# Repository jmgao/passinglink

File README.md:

Moved to [passinglink/passinglink](https://github.com/passinglink/passinglink)

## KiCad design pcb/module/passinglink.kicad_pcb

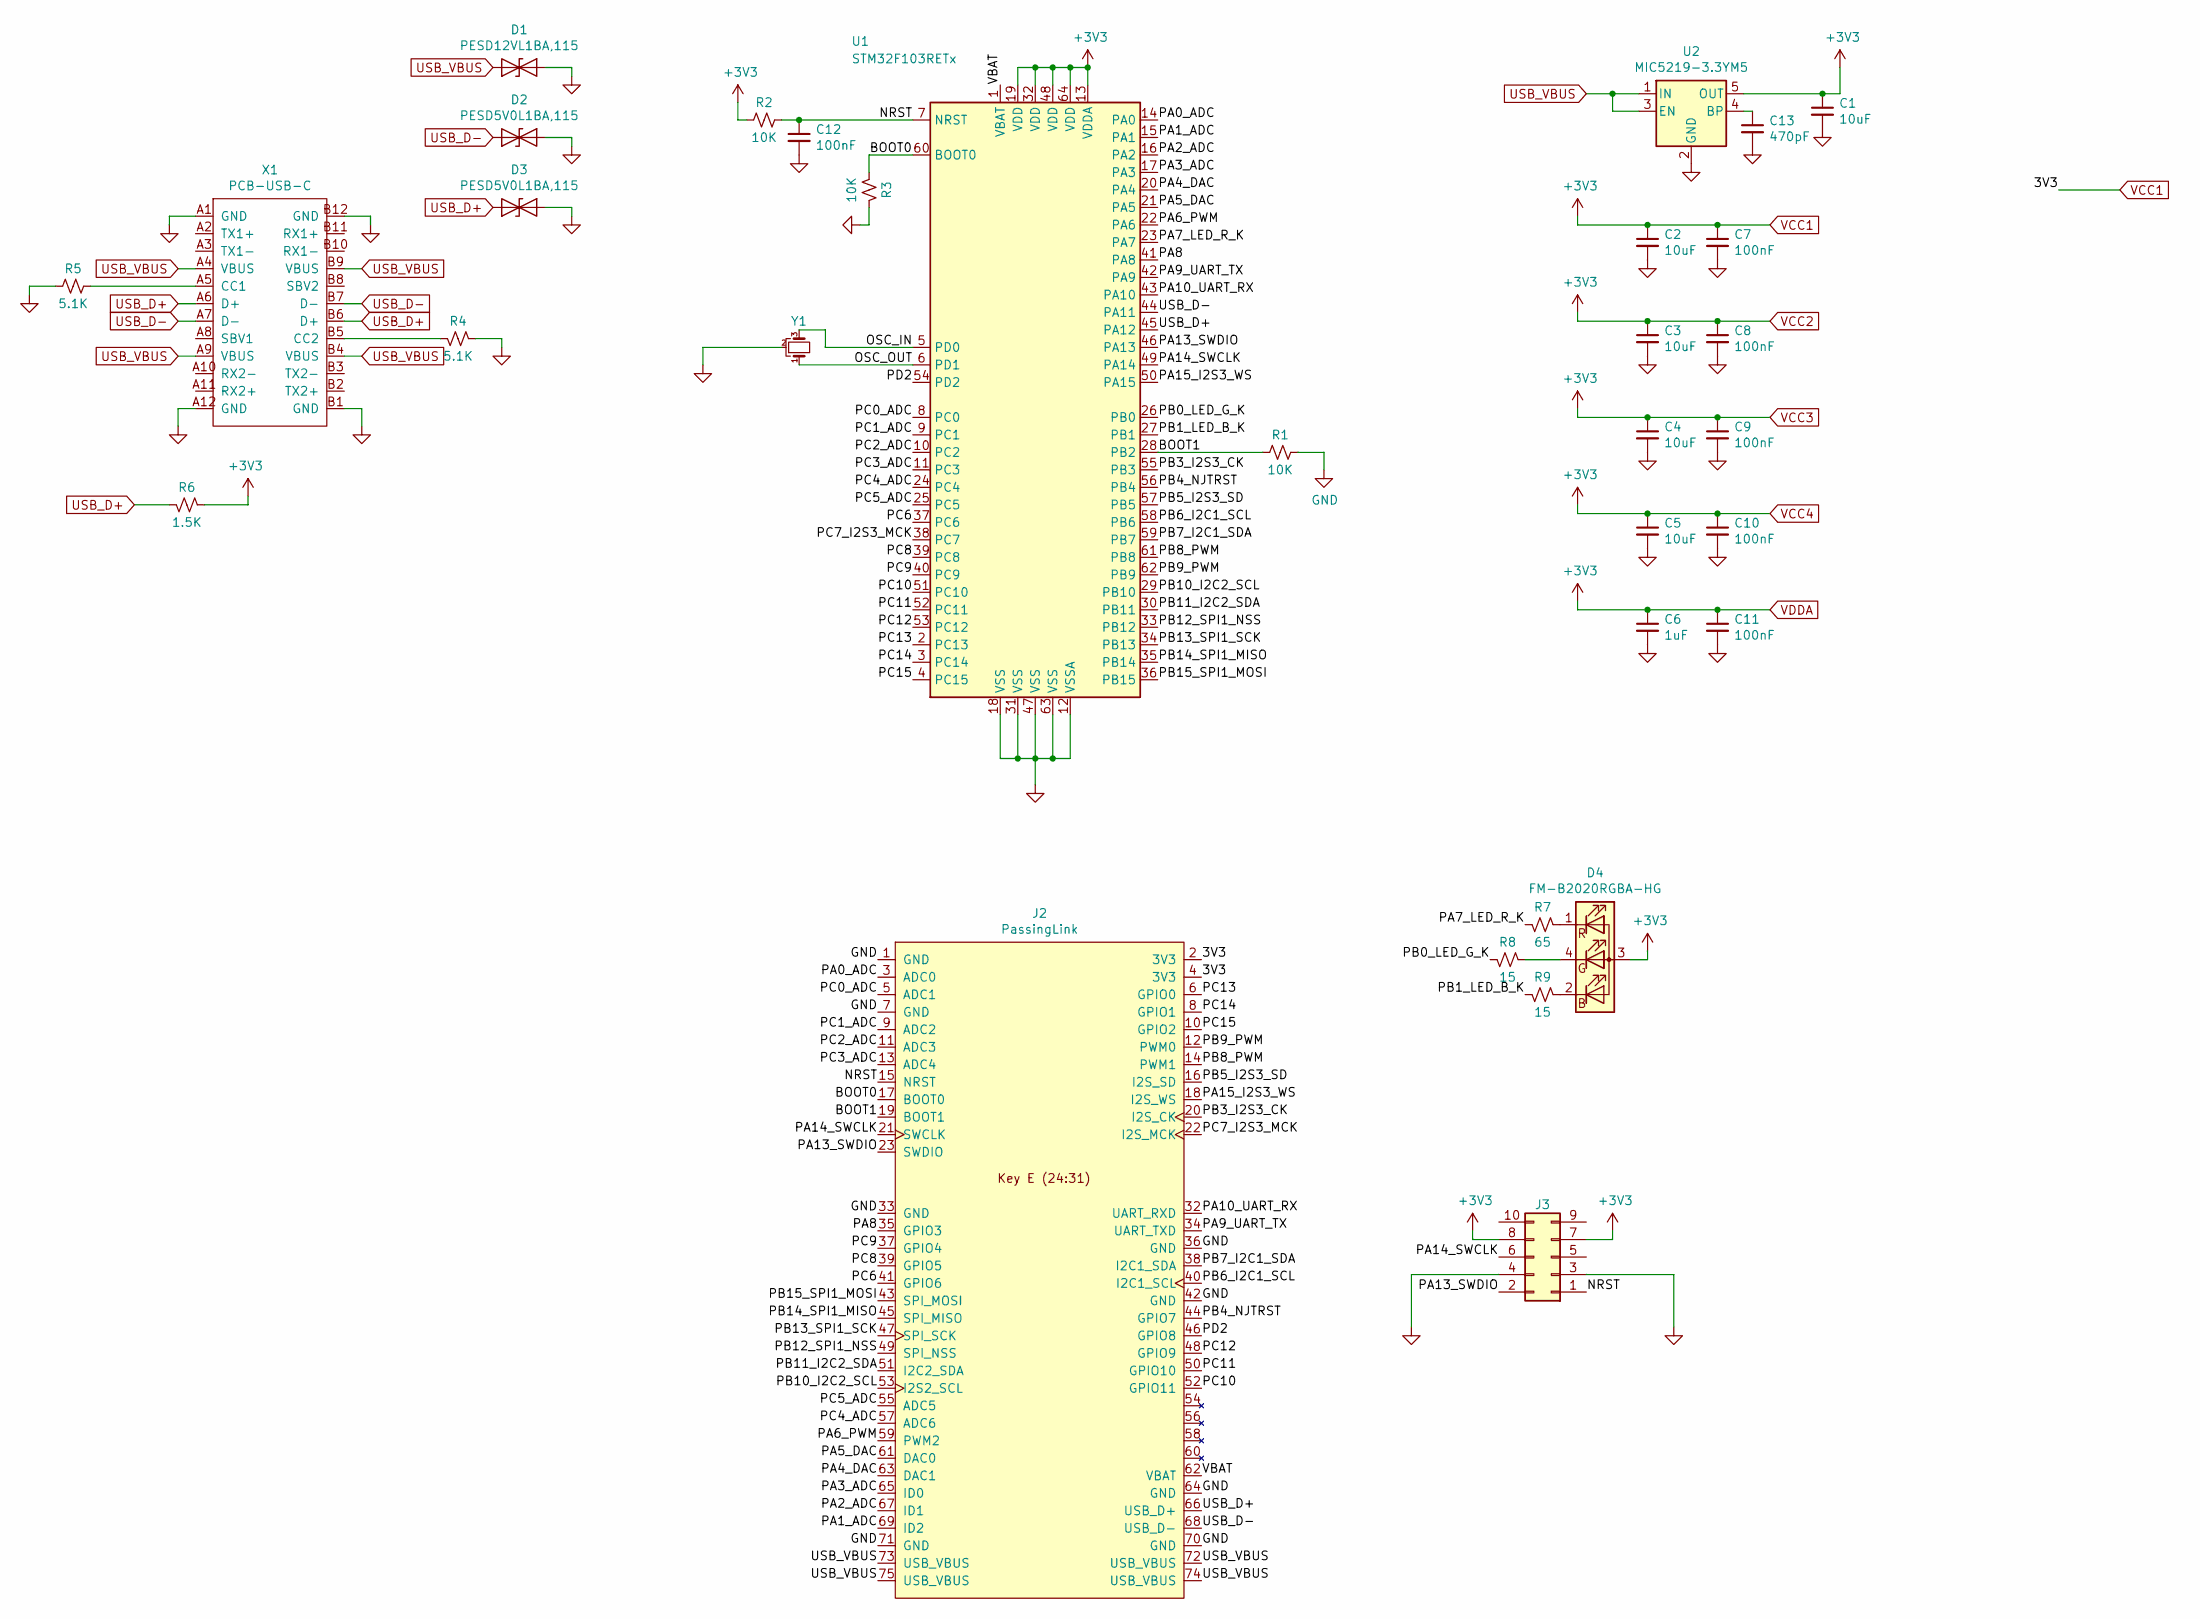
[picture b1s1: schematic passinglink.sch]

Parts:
C1, C2, C3, C4, C5: 10uF; C_0603_1608Metric
C6: 1uF; C_0603_1608Metric
C7, C8, C9, C10, C11, C12: 100nF; C_0603_1608Metric
C13: 470pF; C_0603_1608Metric
D1: PESD12VL1BA,115; D_SOD-323
D2, D3: PESD5V0L1BA,115; D_SOD-323
D4: FM-B2020RGBA-HG
J2: PassingLink; NGFF_E
J3: Conn_02x05_Odd_Even; Tag-Connect_TC2050-IDC-NL_2x05_P1.27mm_Vertical
R1, R2, R3: 10K; R_0603_1608Metric
R4, R5: 5.1K; R_0603_1608Metric
R6: 1.5K; R_0603_1608Metric
R7: 65; R_0603_1608Metric
R8, R9: 15; R_0603_1608Metric
U1: STM32F103RETx; LQFP-64_10x10mm_P0.5mm
U2: MIC5219-3.3YM5; SOT-23-5
X1: PCB-USB-C
Y1: Crystal_GND2_Small; Resonator_SMD_muRata_CSTxExxV-3Pin_3.0x1.1mm

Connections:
/BOOT0: J2.17 (BOOT0), R3.1, U1.60 (BOOT0)
/BOOT1: J2.19 (BOOT1), R1.2, U1.28 (PB2)
/NRST: C12.1, J2.15 (NRST), J3.1, R2.1, U1.7 (NRST)
/OSC_IN: U1.5 (PD0), Y1.3
/OSC_OUT: U1.6 (PD1), Y1.1
/PA0_ADC: J2.3 (ADC0), U1.14 (PA0)
/PA1_ADC: J2.69 (ID2), U1.15 (PA1)
/PA2_ADC: J2.67 (ID1), U1.16 (PA2)
/PA3_ADC: J2.65 (ID0), U1.17 (PA3)
/PA4_DAC: J2.63 (DAC1), U1.20 (PA4)
/PA5_DAC: J2.61 (DAC0), U1.21 (PA5)
/PA6_PWM: J2.59 (PWM2), U1.22 (PA6)
/PA7_LED_R_K: R7.1, U1.23 (PA7)
/PA8: J2.35 (GPIO3), U1.41 (PA8)
/PA9_UART_TX: J2.34 (UART_TXD), U1.42 (PA9)
/PA10_UART_RX: J2.32 (UART_RXD), U1.43 (PA10)
/PA13_SWDIO: J2.23 (SWDIO), J3.2, U1.46 (PA13)
/PA14_SWCLK: J2.21 (SWCLK), J3.6, U1.49 (PA14)
/PA15_I2S3_WS: J2.18 (I2S_WS), U1.50 (PA15)
/PB0_LED_G_K: R8.1, U1.26 (PB0)
/PB1_LED_B_K: R9.1, U1.27 (PB1)
/PB3_I2S3_CK: J2.20 (I2S_CK), U1.55 (PB3)
/PB4_NJTRST: J2.44 (GPIO7), U1.56 (PB4)
/PB5_I2S3_SD: J2.16 (I2S_SD), U1.57 (PB5)
/PB6_I2C1_SCL: J2.40 (I2C1_SCL), U1.58 (PB6)
/PB7_I2C1_SDA: J2.38 (I2C1_SDA), U1.59 (PB7)
/PB8_PWM: J2.14 (PWM1), U1.61 (PB8)
/PB9_PWM: J2.12 (PWM0), U1.62 (PB9)
/PB10_I2C2_SCL: J2.53 (I2S2_SCL), U1.29 (PB10)
/PB11_I2C2_SDA: J2.51 (I2C2_SDA), U1.30 (PB11)
/PB12_SPI1_NSS: J2.49 (SPI_NSS), U1.33 (PB12)
/PB13_SPI1_SCK: J2.47 (SPI_SCK), U1.34 (PB13)
/PB14_SPI1_MISO: J2.45 (SPI_MISO), U1.35 (PB14)
/PB15_SPI1_MOSI: J2.43 (SPI_MOSI), U1.36 (PB15)
/PC0_ADC: J2.5 (ADC1), U1.8 (PC0)
/PC1_ADC: J2.9 (ADC2), U1.9 (PC1)
/PC2_ADC: J2.11 (ADC3), U1.10 (PC2)
/PC3_ADC: J2.13 (ADC4), U1.11 (PC3)
/PC4_ADC: J2.57 (ADC6), U1.24 (PC4)
/PC5_ADC: J2.55 (ADC5), U1.25 (PC5)
/PC6: J2.41 (GPIO6), U1.37 (PC6)
/PC7_I2S3_MCK: J2.22 (I2S_MCK), U1.38 (PC7)
/PC8: J2.39 (GPIO5), U1.39 (PC8)
/PC9: J2.37 (GPIO4), U1.40 (PC9)
/PC10: J2.52 (GPIO11), U1.51 (PC10)
/PC11: J2.50 (GPIO10), U1.52 (PC11)
/PC12: J2.48 (GPIO9), U1.53 (PC12)
/PC13: J2.6 (GPIO0), U1.2 (PC13)
/PC14: J2.8 (GPIO1), U1.3 (PC14)
/PC15: J2.10 (GPIO2), U1.4 (PC15)
/PD2: J2.46 (GPIO8), U1.54 (PD2)
/VBAT: J2.62 (VBAT), U1.1 (VBAT)
GND: C1.2, C2.2, C3.2, C4.2, C5.2, C6.2, C7.2, C8.2, C9.2, C10.2, C11.2, C12.2, C13.2, D1.2 (A2), D2.2 (A2), D3.2 (A2), J2.1 (GND), J2.7 (GND), J2.33 (GND), J2.36 (GND), J2.42 (GND), J2.64 (GND), J2.70 (GND), J2.71 (GND), J3.3, J3.4, R1.1, R3.2, R4.2, R5.2, U1.12 (VSSA), U1.18 (VSS), U1.31 (VSS), U1.47 (VSS), U1.63 (VSS), U2.2 (GND), X1.A1 (GND), X1.A12 (GND), X1.B1 (GND), X1.B12 (GND), Y1.2
unnamed: C13.1, U2.4 (BP)
unnamed: D4.1 (R-), R7.2
unnamed: D4.2 (B-), R9.2
unnamed: D4.4 (G-), R8.2
unnamed: R4.1, X1.B5 (CC2)
unnamed: R5.1, X1.A5 (CC1)
USB_D+: D3.1 (A1), J2.66 (USB_D+), R6.1, U1.45 (PA12), X1.A6 (D+), X1.B6 (D+)
USB_D-: D2.1 (A1), J2.68 (USB_D-), U1.44 (PA11), X1.A7 (D-), X1.B7 (D-)
USB_VBUS: D1.1 (A1), J2.72 (USB_VBUS), J2.73 (USB_VBUS), J2.74 (USB_VBUS), J2.75 (USB_VBUS), U2.1 (IN), U2.3 (EN), X1.A4 (VBUS), X1.A9 (VBUS), X1.B4 (VBUS), X1.B9 (VBUS)
VCC1: C1.1, C2.1, C3.1, C4.1, C5.1, C6.1, C7.1, C8.1, C9.1, C10.1, C11.1, D4.3 (+), J2.2 (3V3), J2.4 (3V3), J3.7, J3.8, R2.2, R6.2, U1.13 (VDDA), U1.19 (VDD), U1.32 (VDD), U1.48 (VDD), U1.64 (VDD), U2.5 (OUT)

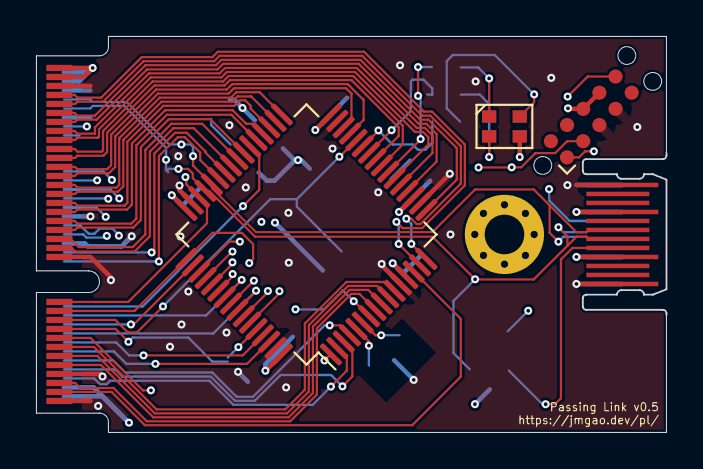
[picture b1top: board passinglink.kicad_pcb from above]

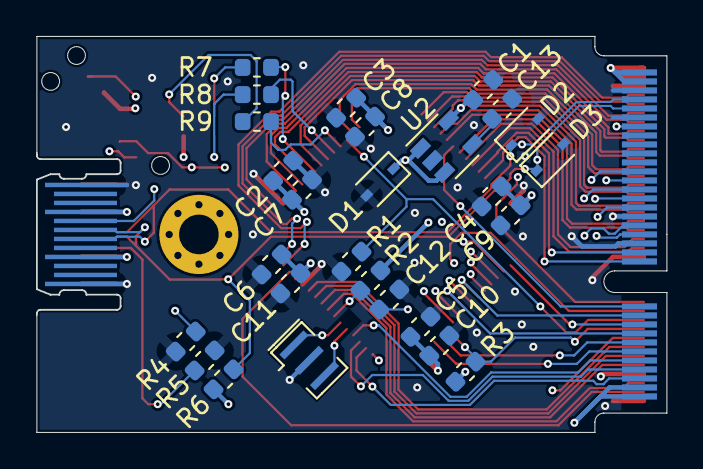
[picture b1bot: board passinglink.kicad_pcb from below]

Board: 4 copper layers, 35.0 x 22.0 mm, 33 parts (27 on the bottom side), 63 nets.

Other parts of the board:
H1: MountingHole_2.2mm_M2_Pad_Via

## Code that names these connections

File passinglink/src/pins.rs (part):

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  use stm32f1xx_hal::gpio::{Input, Output, PullUp, PushPull};

  pub struct InputPins {
    pub stick_down: PB5<Input<PullUp>>,
    pub stick_up: PB6<Input<PullUp>>,
    pub stick_left: PB7<Input<PullUp>>,
    pub stick_right: PB8<Input<PullUp>>,

    pub button_north: PC11<Input<PullUp>>,
    pub button_east: PA9<Input<PullUp>>,
    pub button_south: PA10<Input<PullUp>>,
    pub button_west: PC10<Input<PullUp>>,

    pub button_l1: PD2<Input<PullUp>>,
    pub button_r1: PC12<Input<PullUp>>,

    pub button_l2: PC9<Input<PullUp>>,
    pub button_r2: PA8<Input<PullUp>>,

    pub button_l3: PA7<Input<PullUp>>,
    pub button_r3: PB11<Input<PullUp>>,

    pub button_home: PB1<Input<PullUp>>,
    pub button_start: PC7<Input<PullUp>>,
    pub button_select: PC8<Input<PullUp>>,

    pub button_trackpad: PA6<Input<PullUp>>,

    pub mode_lock: PB0<Input<PullUp>>,
    pub mode_ls: PC5<Input<PullUp>>,
    pub mode_rs: PC4<Input<PullUp>>,
    pub mode_ps3: PB10<Input<PullUp>>,
  }

  macro_rules! assign_inputs {
    ($gpioa: expr, $gpiob: expr, $gpioc: expr, $gpiod: expr) => {{
      InputPins {
        stick_down: $gpiob.pb5.into_pull_up_input(&mut $gpiob.crl),
        stick_up: $gpiob.pb6.into_pull_up_input(&mut $gpiob.crl),
        stick_left: $gpiob.pb7.into_pull_up_input(&mut $gpiob.crl),
        stick_right: $gpiob.pb8.into_pull_up_input(&mut $gpiob.crh),

        button_north: $gpioc.pc11.into_pull_up_input(&mut $gpioc.crh),
        button_east: $gpioa.pa9.into_pull_up_input(&mut $gpioa.crh),
        button_south: $gpioa.pa10.into_pull_up_input(&mut $gpioa.crh),
        button_west: $gpioc.pc10.into_pull_up_input(&mut $gpioc.crh),

        button_l1: $gpiod.pd2.into_pull_up_input(&mut $gpiod.crl),
        button_r1: $gpioc.pc12.into_pull_up_input(&mut $gpioc.crh),

        button_l2: $gpioc.pc9.into_pull_up_input(&mut $gpioc.crh),
        button_r2: $gpioa.pa8.into_pull_up_input(&mut $gpioa.crh),

        button_l3: $gpioa.pa7.into_pull_up_input(&mut $gpioa.crl),
        button_r3: $gpiob.pb11.into_pull_up_input(&mut $gpiob.crh),

        button_home: $gpiob.pb1.into_pull_up_input(&mut $gpiob.crl),
        button_start: $gpioc.pc7.into_pull_up_input(&mut $gpioc.crl),
        button_select: $gpioc.pc8.into_pull_up_input(&mut $gpioc.crh),
        button_trackpad: $gpioa.pa6.into_pull_up_input(&mut $gpioa.crl),

        mode_lock: $gpiob.pb0.into_pull_up_input(&mut $gpiob.crl),
        mode_ls: $gpioc.pc5.into_pull_up_input(&mut $gpioc.crl),
        mode_rs: $gpioc.pc4.into_pull_up_input(&mut $gpioc.crl),
        mode_ps3: $gpiob.pb10.into_pull_up_input(&mut $gpiob.crh),
      }
    }};
  }

  pub struct LedPins {
    pub front: PC6<Output<PushPull>>,
    pub pcb_r: Option<PCx<Output<PushPull>>>,
    pub pcb_g: Option<PCx<Output<PushPull>>>,
    pub pcb_b: Option<PCx<Output<PushPull>>>,
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  macro_rules! assign_leds {
    ($gpioa: expr, $gpiob: expr, $gpioc: expr, $gpiod: expr) => {{
      LedPins {
        front: $gpioc.pc6.into_push_pull_output(&mut $gpioc.crl),
        pcb_r: None,
        pcb_g: None,
        pcb_b: None,
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  use stm32f1xx_hal::gpio::{Input, Output, PullUp, PushPull};

  pub struct InputPins {
    pub stick_down: PA10<Input<PullUp>>,
    pub stick_up: PA9<Input<PullUp>>,
    pub stick_left: PA8<Input<PullUp>>,
    pub stick_right: PC9<Input<PullUp>>,

    pub button_north: PC6<Input<PullUp>>,
    pub button_east: PB13<Input<PullUp>>,
    pub button_south: PB14<Input<PullUp>>,
    pub button_west: PB15<Input<PullUp>>,

    pub button_l1: PC8<Input<PullUp>>,
    pub button_r1: PC7<Input<PullUp>>,

    pub button_l2: PB11<Input<PullUp>>,
    pub button_r2: PB12<Input<PullUp>>,

    pub button_l3: PC12<Input<PullUp>>,
    pub button_r3: PD2<Input<PullUp>>,

    pub button_home: PC15<Input<PullUp>>,
    pub button_start: PC4<Input<PullUp>>,
    pub button_select: PB10<Input<PullUp>>,
    pub button_trackpad: PB5<Input<PullUp>>,

    pub mode_lock: PC14<Input<PullUp>>,
    pub mode_ls: PC13<Input<PullUp>>,
    pub mode_rs: PC10<Input<PullUp>>,
    pub mode_ps3: PC11<Input<PullUp>>,
  }

  macro_rules! assign_inputs {
    ($gpioa: expr, $gpiob: expr, $gpioc: expr, $gpiod: expr) => {{
      InputPins {
        stick_down: $gpioa.pa10.into_pull_up_input(&mut $gpioa.crh),
        stick_up: $gpioa.pa9.into_pull_up_input(&mut $gpioa.crh),
        stick_left: $gpioa.pa8.into_pull_up_input(&mut $gpioa.crh),
        stick_right: $gpioc.pc9.into_pull_up_input(&mut $gpioc.crh),

        button_north: $gpioc.pc6.into_pull_up_input(&mut $gpioc.crl),
        button_east: $gpiob.pb13.into_pull_up_input(&mut $gpiob.crh),
        button_south: $gpiob.pb14.into_pull_up_input(&mut $gpiob.crh),
        button_west: $gpiob.pb15.into_pull_up_input(&mut $gpiob.crh),

        button_l1: $gpioc.pc8.into_pull_up_input(&mut $gpioc.crh),
        button_r1: $gpioc.pc7.into_pull_up_input(&mut $gpioc.crl),

        button_l2: $gpiob.pb11.into_pull_up_input(&mut $gpiob.crh),
        button_r2: $gpiob.pb12.into_pull_up_input(&mut $gpiob.crh),

        button_l3: $gpioc.pc12.into_pull_up_input(&mut $gpioc.crh),
        button_r3: $gpiod.pd2.into_pull_up_input(&mut $gpiod.crl),

        button_home: $gpioc.pc15.into_pull_up_input(&mut $gpioc.crh),
        button_start: $gpioc.pc4.into_pull_up_input(&mut $gpioc.crl),
        button_select: $gpiob.pb10.into_pull_up_input(&mut $gpiob.crh),
        button_trackpad: $gpiob.pb5.into_pull_up_input(&mut $gpiob.crl),

        mode_lock: $gpioc.pc14.into_pull_up_input(&mut $gpioc.crh),
        mode_ls: $gpioc.pc13.into_pull_up_input(&mut $gpioc.crh),
        mode_rs: $gpioc.pc10.into_pull_up_input(&mut $gpioc.crh),
        mode_ps3: $gpioc.pc11.into_pull_up_input(&mut $gpioc.crh),
      }
    }};
  }

  pub struct LedPins {
    pub front: PA6<Output<PushPull>>,
    pub pcb_r: Option<PA7<Output<PushPull>>>,
    pub pcb_g: Option<PB0<Output<PushPull>>>,
    pub pcb_b: Option<PB1<Output<PushPull>>>,
  }

  macro_rules! assign_leds {
    ($gpioa: expr, $gpiob: expr, $gpioc: expr, $gpiod: expr) => {{
      LedPins {
        front: $gpioa.pa6.into_push_pull_output(&mut $gpioa.crl),
        pcb_r: Some($gpioa.pa7.into_push_pull_output(&mut $gpioa.crl)),
        pcb_g: Some($gpiob.pb0.into_push_pull_output(&mut $gpiob.crl)),
        pcb_b: Some($gpiob.pb1.into_push_pull_output(&mut $gpiob.crl)),
      }
    }}
  }
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  use stm32f1xx_hal::gpio::{Input, Output, PullUp, PushPull};

  pub struct InputPins {
    pub stick_down: PB9<Input<PullUp>>,
    pub stick_up: PB8<Input<PullUp>>,
    pub stick_left: PB7<Input<PullUp>>,
    pub stick_right: PB6<Input<PullUp>>,

    pub button_north: PC14<Input<PullUp>>,
    pub button_east: PC15<Input<PullUp>>,
    pub button_south: PA0<Input<PullUp>>,
    pub button_west: PA1<Input<PullUp>>,

    pub button_l1: PA4<Input<PullUp>>,
    pub button_r1: PA5<Input<PullUp>>,

    pub button_l2: PA6<Input<PullUp>>,
    pub button_r2: PA7<Input<PullUp>>,

    pub button_l3: PB0<Input<PullUp>>,
    pub button_r3: PB1<Input<PullUp>>,

    pub button_home: PB15<Input<PullUp>>,
    pub button_start: PB14<Input<PullUp>>,
    pub button_select: PB13<Input<PullUp>>,
    pub button_trackpad: PB12<Input<PullUp>>,

    pub mode_lock: PB5<Input<PullUp>>,
    pub mode_ls: PA10<Input<PullUp>>,
    pub mode_rs: PA9<Input<PullUp>>,
    pub mode_ps3: PA8<Input<PullUp>>,
  }

  macro_rules! assign_inputs {
    ($gpioa: expr, $gpiob: expr, $gpioc: expr, $gpiod: expr) => {{
      InputPins {
        stick_down: $gpiob.pb9.into_pull_up_input(&mut $gpiob.crh),
        stick_up: $gpiob.pb8.into_pull_up_input(&mut $gpiob.crh),
        stick_left: $gpiob.pb7.into_pull_up_input(&mut $gpiob.crl),
        stick_right: $gpiob.pb6.into_pull_up_input(&mut $gpiob.crl),

        button_north: $gpioc.pc14.into_pull_up_input(&mut $gpioc.crh),
        button_east: $gpioc.pc15.into_pull_up_input(&mut $gpioc.crh),
        button_south: $gpioa.pa0.into_pull_up_input(&mut $gpioa.crl),
        button_west: $gpioa.pa1.into_pull_up_input(&mut $gpioa.crl),

        button_l1: $gpioa.pa4.into_pull_up_input(&mut $gpioa.crl),
        button_r1: $gpioa.pa5.into_pull_up_input(&mut $gpioa.crl),

        button_l2: $gpioa.pa6.into_pull_up_input(&mut $gpioa.crl),
        button_r2: $gpioa.pa7.into_pull_up_input(&mut $gpioa.crl),

        button_l3: $gpiob.pb0.into_pull_up_input(&mut $gpiob.crl),
        button_r3: $gpiob.pb1.into_pull_up_input(&mut $gpiob.crl),

        button_home: $gpiob.pb15.into_pull_up_input(&mut $gpiob.crh),
        button_start: $gpiob.pb14.into_pull_up_input(&mut $gpiob.crh),
        button_select: $gpiob.pb13.into_pull_up_input(&mut $gpiob.crh),
        button_trackpad: $gpiob.pb12.into_pull_up_input(&mut $gpiob.crh),

        mode_lock: $gpiob.pb5.into_pull_up_input(&mut $gpiob.crl),
        mode_ls: $gpioa.pa10.into_pull_up_input(&mut $gpioa.crh),
        mode_rs: $gpioa.pa9.into_pull_up_input(&mut $gpioa.crh),
        mode_ps3: $gpioa.pa8.into_pull_up_input(&mut $gpioa.crh),
      }
    }};
  }

  pub struct LedPins {
    pub front: PC13<Output<PushPull>>,
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
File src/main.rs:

#![no_main]
#![no_std]
#![allow(non_snake_case)]
#![feature(asm)]

extern crate panic_semihosting;

#[macro_use]
extern crate log;

#[macro_use]
extern crate proper;

use core::fmt::Write;

use cortex_m::interrupt;

use rtfm::app;
use rtfm::Instant;

use stm32f1xx_hal::gpio;
use stm32f1xx_hal::prelude::*;
use stm32f1xx_hal::serial::{Parity, Serial, StopBits};

use stm32_usbd::{UsbBus, UsbBusType};
use usb_device::bus;
use usb_device::prelude::*;

mod hid;

mod input;
use input::DeviceInputs;
use input::Hat;

mod serial;
use serial::BufferedSerial;

const VERSION: &'static str = env!("CARGO_PKG_VERSION");

static mut SERIAL: Option<BufferedSerial> = None;
static mut INPUTS: DeviceInputs = DeviceInputs::default();

#[app(device = stm32f1xx_hal::stm32)]
const APP: () = {
  static mut LED: gpio::gpioc::PC13<gpio::Output<gpio::PushPull>> = ();

  static mut USB_DEV: UsbDevice<'static, UsbBusType> = ();
  static mut USB_HID: hid::HidClass<'static, hid::PS4Hid, UsbBusType> = ();

  #[init(schedule = [timer_tick, input_poll])]
  fn init() {
    static mut USB_BUS: Option<bus::UsbBusAllocator<UsbBusType>> = None;

    let mut flash = device.FLASH.constrain();
    let mut rcc = device.RCC.constrain();

    let clocks = rcc
      .cfgr
      .use_hse(8.mhz())
      .sysclk(72.mhz())
      .pclk1(24.mhz())
      .freeze(&mut flash.acr);

    assert!(clocks.usbclk_valid());

    let mut gpioc = device.GPIOC.split(&mut rcc.apb2);
    let mut led = gpioc.pc13.into_push_pull_output(&mut gpioc.crh);
    led.set_high();

    let mut afio = device.AFIO.constrain(&mut rcc.apb2);
    let mut gpioa = device.GPIOA.split(&mut rcc.apb2);

    let pin_tx = gpioa.pa2.into_alternate_push_pull(&mut gpioa.crl);
    let pin_rx = gpioa.pa3;

    let serial_config = stm32f1xx_hal::serial::Config {
      baudrate: 921_600.bps(),
      parity: Parity::ParityNone,
      stopbits: StopBits::STOP1,
    };

    let serial = Serial::usart2(
      device.USART2,
      (pin_tx, pin_rx),
      &mut afio.mapr,
      serial_config,
      clocks,
      &mut rcc.apb1,
    );

    let mut buffered_serial = BufferedSerial::new(serial);

    unsafe {
      let _ = write!(buffered_serial, "\r\n\r\n");
      SERIAL = Some(buffered_serial);
      log::set_logger(SERIAL.as_ref().unwrap()).unwrap();
      log::set_max_level(log::LevelFilter::Trace);
    }
    info!("passinglink v{} initialized", VERSION);
    schedule.timer_tick(Instant::now() + 7_200_000.cycles()).unwrap();

    // BluePill board has a pull-up resistor on the D+ line.
    // Pull the D+ pin down to send a RESET condition to the USB bus.
    let mut usb_dp = gpioa.pa12.into_push_pull_output(&mut gpioa.crh);
    usb_dp.set_low();
    cortex_m::asm::delay(clocks.sysclk().0 / 100);

    let usb_dm = gpioa.pa11;
    let usb_dp = usb_dp.into_floating_input(&mut gpioa.crh);

    *USB_BUS = Some(UsbBus::new(device.USB, (usb_dm, usb_dp)));

    let ps4_hid = hid::PS4Hid::new(unsafe { &mut INPUTS as *mut DeviceInputs });
    let usb_hid = hid::HidClass::new(ps4_hid, USB_BUS.as_ref().unwrap());
    let usb_dev = UsbDeviceBuilder::new(USB_BUS.as_ref().unwrap(), UsbVidPid(0x1209, 0x214D))
      .manufacturer("jmgao")
      .product("Passing Link")
      .serial_number("66C623A66B214BB226X76C236B214A214CC6C236B")
      .device_class(0x00)
      .device_sub_class(0x00)
      .max_power(500)
      .max_packet_size_0(64)
      .build();

    schedule.input_poll(Instant::now() + 72_000.cycles()).unwrap();

    LED = led;
    USB_DEV = usb_dev;
    USB_HID = usb_hid;
  }

  #[task(priority = 1, schedule = [input_poll], resources = [USB_DEV, USB_HID])]
  fn input_poll() {
    interrupt::free(|_| unsafe {
      static mut COUNTER: u32 = 0;
      COUNTER = COUNTER.wrapping_add(1);

      // Press home once after 1 second, then 2 seconds later X, and then start doing SPDs every 17 milliseconds after.
      if COUNTER == 1000 {
        INPUTS.button_home.set();
      } else if COUNTER == 1250 {
        INPUTS.button_home.clear();
      } else if COUNTER == 3000 {
        INPUTS.button_south.set();
      } else if COUNTER == 3250 {
        INPUTS.button_south.clear();
      } else if COUNTER == 4000 {
        INPUTS.button_east.set();
      } else if COUNTER == 4250 {
        INPUTS.button_east.clear();
      } else if COUNTER > 5000 {
        let input = COUNTER / 17;
        INPUTS.hat_dpad = match input % 8 {
          0 => Hat::North,
          1 => Hat::NorthEast,
          2 => Hat::East,
          3 => Hat::SouthEast,
          4 => Hat::South,
          5 => Hat::SouthWest,
          6 => Hat::West,
          7 => Hat::NorthWest,
          _ => unreachable!(),
        };
      }
    });

    resources.USB_HID.send();
    schedule.input_poll(scheduled + 72_000.cycles()).unwrap();
  }

  #[task(priority = 16, schedule = [timer_tick], resources = [LED])]
  fn timer_tick() {
    resources.LED.toggle();

    unsafe {
      if let Some(ref mut buffered_serial) = SERIAL {
        buffered_serial.tick();
      }
    }

    schedule.timer_tick(scheduled + 72_000_000.cycles()).unwrap();
  }

  #[interrupt]
  fn USART2() {
    unsafe {
      if let Some(ref mut serial) = SERIAL {
        serial.poll();
      }
    }
  }

  #[interrupt(resources = [USB_DEV, USB_HID])]
  fn USB_HP_CAN_TX() {
    usb_poll(&mut resources.USB_DEV, &mut resources.USB_HID);
  }

  #[interrupt(resources = [USB_DEV, USB_HID])]
  fn USB_LP_CAN_RX0() {
    usb_poll(&mut resources.USB_DEV, &mut resources.USB_HID);
  }

  extern "C" {
    fn EXTI0();
    fn EXTI1();
  }

  #[idle]
  fn idle() -> ! {
    loop {
      unsafe {
        asm!("nop");
      }
    }
  }
};

fn usb_poll<B: bus::UsbBus>(usb_dev: &mut UsbDevice<'static, B>, hid: &mut hid::HidClass<'static, hid::PS4Hid, B>) {
  if !usb_dev.poll(&mut [hid]) {
    return;
  }
}

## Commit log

2019-06-10 Initial commit of skeleton project.
2019-06-10 Clean up dependencies.
2019-06-10 Make `cargo run` play well with cargo-watch.
2019-06-10 Replace empty idle loop with a nop.
    LLVM defines an infinite loop with no side effects as undefined
    behavior, which leads to a crash when compiled in release mode.
2019-06-10 Implement a buffered serial output.
2019-06-10 Enable debugging information on release builds.
2019-06-10 Don't set breakpoints by default.
    They don't always get cleared when we exit, which eventually leads to
    exhaustion of hardware breakpoints.
2019-06-10 Rename periodic to timer_tick.
2019-06-10 Use the serial console for logging.
2019-06-10 Switch linker script to use 64kB of flash.
2019-06-11 Write "\r\n\r\n" when initializing serial.
    We can get stray garbage across the serial console while booting, so
    write some newlines to hopefully move clear of it.
2019-06-11 Enable LTO.
2019-06-11 Update stm32f1xx-hal.
2019-06-13 Implement PS4 HID emulation.
    This doesn't actually implement the PS4's controller authentication,
    which requires an actual private key to be dumped from a controller, but
    it's good enough to work for 10 minutes at a time.
2019-06-20 Add LICENSE.
2019-06-20 Add README.
2019-06-25 Move passinglink into its own directory.
2019-07-10 Switch to stm32-usbd.
2019-07-10 Increase delay in inputs.
2019-07-10 Add the report counter.
2019-07-10 Allow warnings in heapless.
2019-07-12 Reduce image size by a bit.
2019-07-12 Implement DS4 authentication.
2019-07-25 Wire up inputs.
2019-07-26 Update stm32-usbd version.
2019-07-26 Remove LED for now.
2019-07-26 Initialize BufferedSerial cycles to CYCCNT.
2019-07-26 Fix initial timer tick value.
2019-07-26 Schedule timers in idle.
    It appears that a bug in RTFM (japaric/cortex-m-rtfm#196) results in
    tasks scheduled from init to be delayed by ~10 seconds. Move scheduling
    to the top of the idle task to work around this.
2019-07-27 Vendor cortex-m-rtfm.
2019-07-27 Massively overprovision the allocator.
2019-07-27 Unvendor stm32f103xx-usb.
    Upstream is deprecated in favor of stm32-usbd, and we've switched
    over already.
2019-07-27 Update cortex-m-rt.
2019-07-27 Pin specific version of crc.
2019-07-27 Update cortex-m-rtfm's cortex-m dependency.
2019-07-27 Merge upstream into vendored stm32f1xx-hal.
    Also silence warnings.
2019-07-27 Switch to RTFM 5.
2019-07-28 Update USB dependencies
2019-08-08 Switch back to upstream usb-device.
2019-08-08 Add dummy placeholder keys.
2019-08-08 Gracefully handle missing keys.
2019-08-08 Add support for lock switch.
2019-08-08 Set trigger analog values along with buttons.
2019-08-26 Update README.md.
2019-08-26 PCB revision v0.4.
2019-08-26 Extract pin assignment, add support for PCB v0.4.
2019-08-27 Revert "Massively overprovision the allocator."
    This reverts commit 47312898e7972ae071ea3d45f2e46ec44b8c04de.
2019-08-27 Add configuration for bluepill.
2019-08-27 Guard the allocation counter behind a feature.
    Saves 640 bytes of text when disabled, which is just barely enough to
    squeeze onto a 64kB bluepill.
2019-08-29 Fix dpad neutral.
2019-08-29 Implement LS/DPad mode switch.
2019-08-29 WIP: USB DFU bootloader
2019-08-30 Use Ordering::SeqCst in auth.rs.
2019-08-30 Delete dead asm!("nop") loop.
    Infinite loops without side effects are undefined behavior in LLVM, so
    previously, we needed an explicit nop to avoid the loop getting deleted
    and our idle task falling through to whatever was below. We now have a
    loop with side effects that can't get optimized out, so the loop is now
    dead code.
2019-08-30 Improve handling of invalid auth state transitions.
    It seems that on occasion, we will get seemingly invalid auth packets
    (e.g. getting a new nonce before we've sent out the full signature),
    which can result in auth hanging and us getting kicked off after 10
    minutes. This can also happen when disconnecting and reconnecting while
    externally powered.
2019-08-30 Block interrupts in alloc/dealloc.
    There seem to be OOMs happening despite the high water mark being lower
    than the actual number of blocks available. One possible explanation
    would be reentrancy in alloc, so let's rule that out first.
2019-09-03 Rearrange input files.
2019-09-03 Update stm32f1xx-hal version.
2019-09-03 Clarify authentication log message.
2019-09-03 Vendor stm32-usbd.
2019-09-05 Turn off LEDs on start.
2019-10-06 Delay input polling until 900us after a USB read.
    Reduce input latency by waiting until just before we think that a
    subsequent USB read is about to happen.
    This reduces latency from 1.5ms on average to 0.9ms.
2019-10-18 Import NGFF footprint library.
2019-10-18 Prepare to split the PCB into two parts.
2019-10-18 Create symbol for the M.2 connector.
2019-11-01 PCB v0.5.
    Layout a new PCB that connects to an external breakout board via an M.2
    connector.
2019-11-05 Make new nightly warnings in ring non-fatal.
2019-11-05 Unvendor heapless.
2019-11-05 Drop support for bluepill/old PCBs.
2019-11-19 WIP: panthera
2020-02-24 Move to passinglink/passinglink.
